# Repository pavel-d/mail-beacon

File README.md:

# Mail Beacon

The Mailbox Beacon is a device that detects when a new letter or package has been delivered to your mailbox using a reed switch. It sends a signal to your LoRa gateway, then the gateway sends a message via WiFi to MQTT server. It's designed to integrate with HomeAssistant, but can theoretically work with anything that supports MQTT based sensors.

Specification
--
- Microcontroller: Attiny1616
- Radio module: SX1278 LoRa 433 Mhz (Ai-Thinker-Ra-01)
- Sensor: Reed switch
- Voltage regulator: SPX3819M5-L-3-3
- Programming Protocol: UPDI
- Power consumption: in microamps range when asleep
- Gateway: LILYGO TTGO LoRa32 V2.1
- Status LED

Wiring
--
Reed switch (or any other kind of contact switch) must be connected either to PA4 or PA7 pins and to the GND. Pins have internal pull-ups enabled and are "active low", so the switch must pull the pin to the ground when circuit is closed. Both pins have interrupts attached, microcontroller will send a message to the gateway when the logic level changes.

TEST button also has an interrupt attached and can be used to test the setup.

Power LED has a jumper that can be cut to reduce the power consumption.

Battery monitoring
--
The beacon sends the battery voltage (in milivolts) in every LoRa packet, so that you know when you need to re-charge the battery.

Schematic
--

Board
--

Images
--

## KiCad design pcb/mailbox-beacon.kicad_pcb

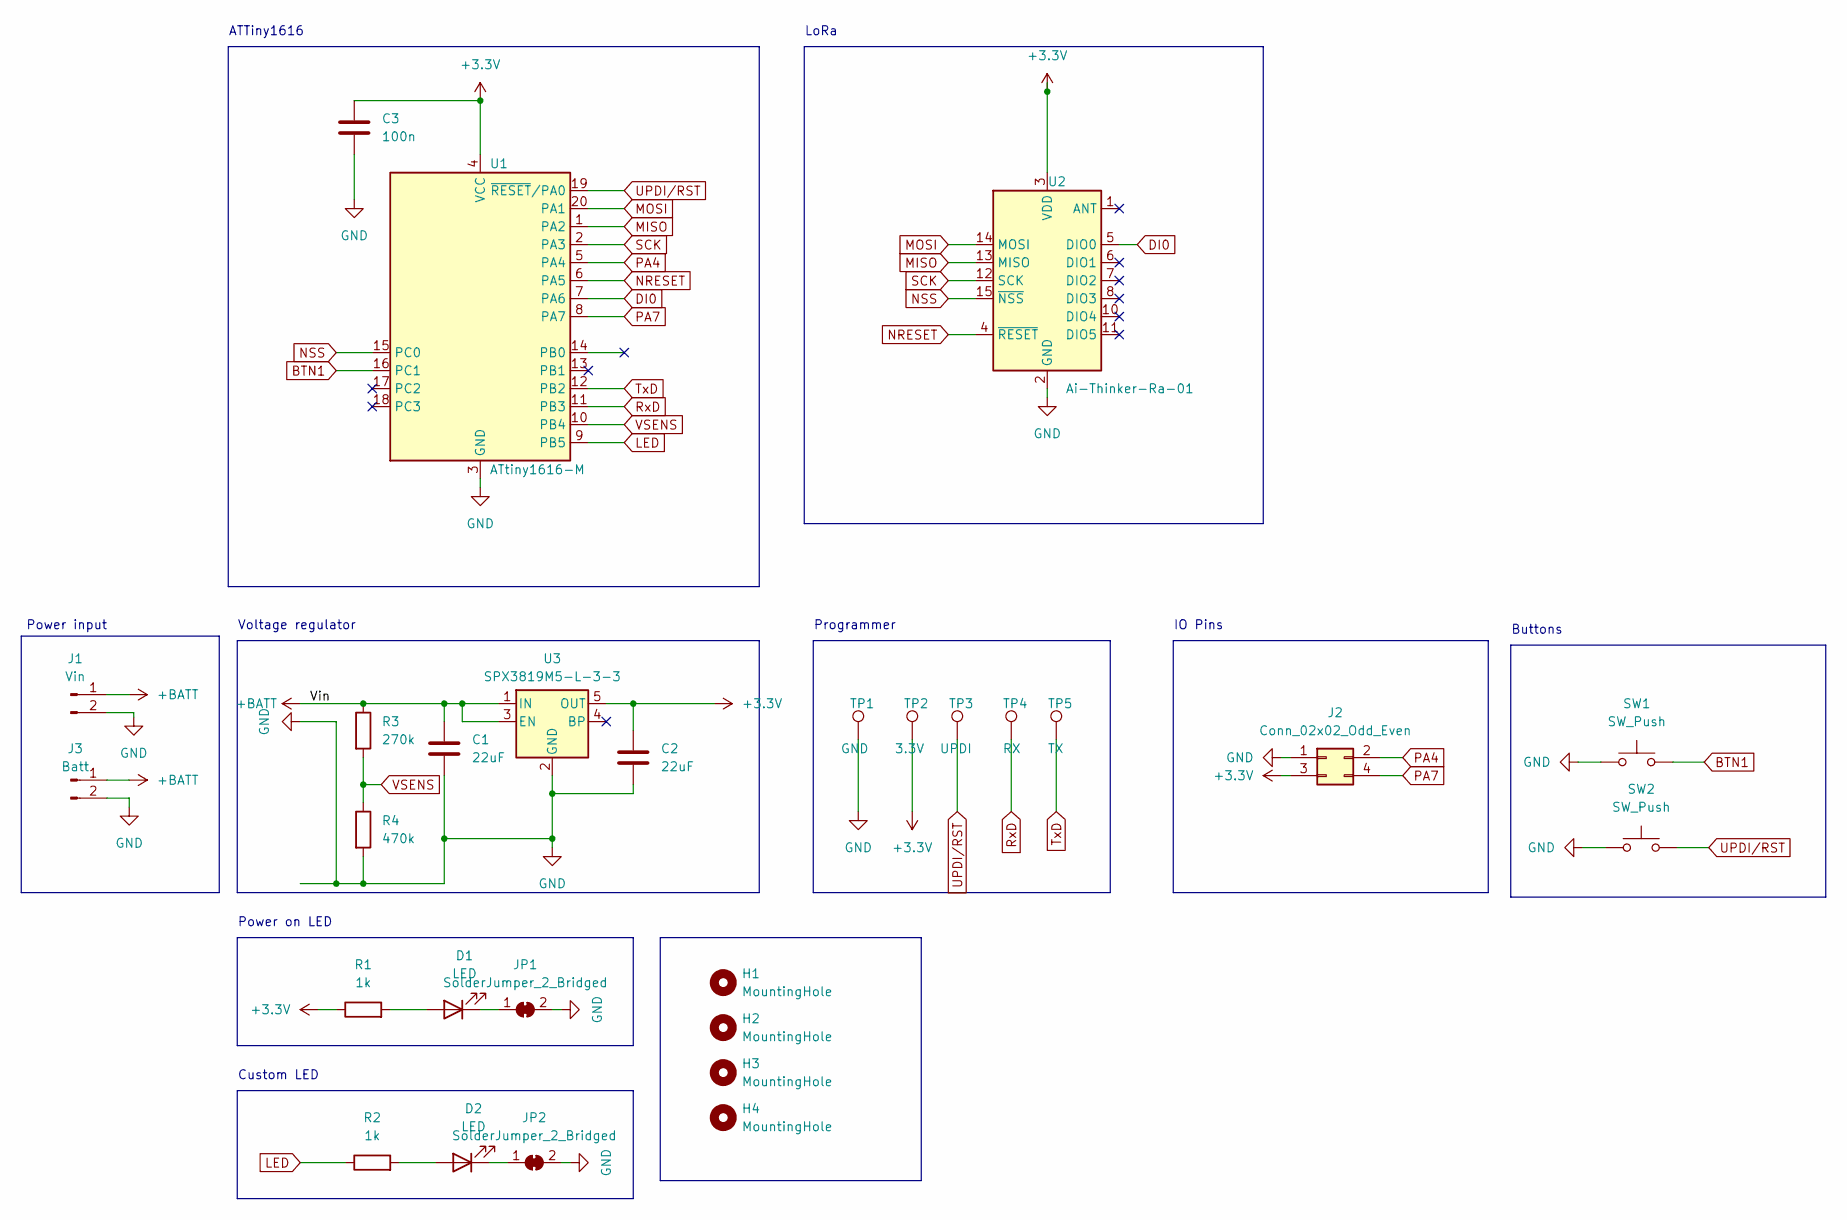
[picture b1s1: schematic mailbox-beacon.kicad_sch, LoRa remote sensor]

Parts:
C1, C2: 22uF; C_0805_2012Metric
C3: 100n; C_0805_2012Metric
D1, D2: LED; LED_0805_2012Metric
H1, H2, H3, H4: MountingHole; MountingHole_2.2mm_M2_Pad
J1: Vin; PinHeader_1x02_P2.54mm_Vertical
J2: Conn_02x02_Odd_Even; PinHeader_2x02_P2.54mm_Vertical
J3: Batt; JST_PH_S2B-PH-K_1x02_P2.00mm_Horizontal
JP1, JP2: SolderJumper_2_Bridged; SolderJumper-2_P1.3mm_Bridged_RoundedPad1.0x1.5mm
R1, R2: 1k; R_0805_2012Metric
R3: 270k; R_0805_2012Metric
R4: 470k; R_0805_2012Metric
SW1, SW2: SW_Push; SW_SPST_B3U-1000P
TP1: GND; TestPoint_Pad_D1.5mm
TP2: 3.3V; TestPoint_Pad_D1.5mm
TP3: UPDI; TestPoint_Pad_D1.5mm
TP4: RX; TestPoint_Pad_D1.5mm
TP5: TX; TestPoint_Pad_D1.5mm
U1: ATtiny1616-M; VQFN-20-1EP_3x3mm_P0.4mm_EP1.7x1.7mm
U2: Ai-Thinker-Ra-01; Ai-Thinker-Ra-01-LoRa
U3: SPX3819M5-L-3-3; SOT-23-5

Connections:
+3.3V: C2.1, C3.1, J2.3, R1.1, TP2.1, U1.4 (VCC), U2.3 (VDD), U3.5 (OUT)
+BATT: C1.1, J1.1, J3.1, R3.1, U3.1 (IN), U3.3 (EN)
BTN1: SW1.2, U1.16 (PC1)
DI0: U1.7 (PA6), U2.5 (DIO0)
GND: C1.2, C2.2, C3.2, J1.2, J2.1, J3.2, JP1.2 (B), JP2.2 (B), R4.2, SW1.1, SW2.1, TP1.1, U1.3 (GND), U1.21 (GND), U2.2 (GND), U2.9 (GND), U2.16 (GND), U3.2 (GND)
LED: R2.1, U1.9 (PB5)
MISO: U1.1 (PA2), U2.13 (MISO)
MOSI: U1.20 (PA1), U2.14 (MOSI)
NRESET: U1.6 (PA5), U2.4 (~RESET)
NSS: U1.15 (PC0), U2.15 (~NSS)
unnamed: D1.2 (A), R1.2
unnamed: D1.1 (K), JP1.1 (A)
unnamed: D2.2 (A), R2.2
unnamed: D2.1 (K), JP2.1 (A)
PA4: J2.2, U1.5 (PA4)
PA7: J2.4, U1.8 (PA7)
RxD: TP4.1, U1.11 (PB3)
SCK: U1.2 (PA3), U2.12 (SCK)
TxD: TP5.1, U1.12 (PB2)
UPDI/RST: SW2.2, TP3.1, U1.19 (~RESET/PA0)
VSENS: R3.2, R4.1, U1.10 (PB4)

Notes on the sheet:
Voltage regulator
IO Pins
Programmer
Buttons
Power on LED
Custom LED
Power input
LoRa
ATTiny1616

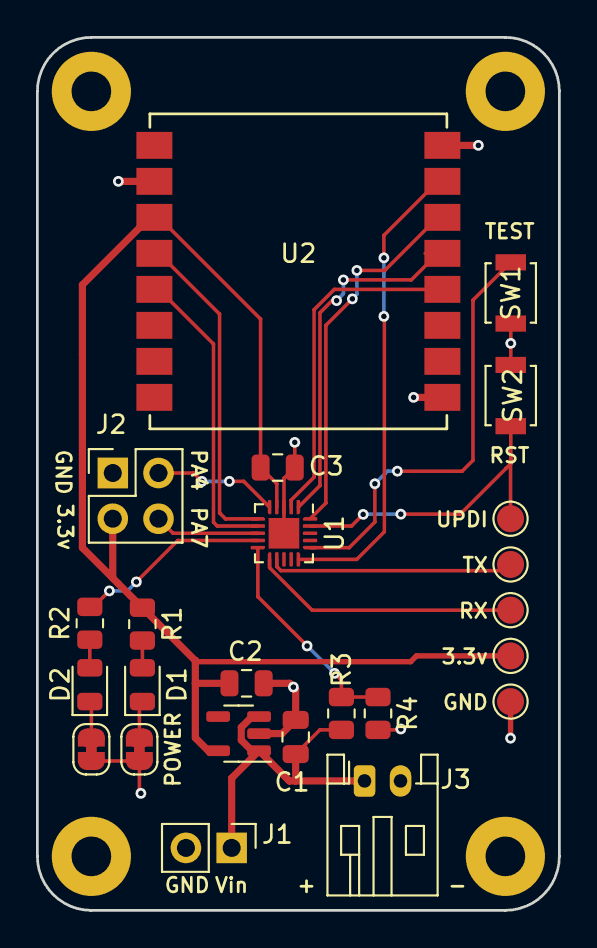
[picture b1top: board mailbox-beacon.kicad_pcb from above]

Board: 2 copper layers, 29.0 x 48.5 mm, 28 parts (0 on the bottom side), 21 nets.

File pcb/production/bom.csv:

Designator,Footprint,Quantity,Value,LCSC Part #
"C1, C2",0805,2,22uF,
C3,0805,1,100n,
"D1, D2",0805,2,LED,
"H1, H2, H3, H4",MountingHole_2.2mm_M2_Pad,4,MountingHole,
J1,PinHeader_1x02_P2.54mm_Vertical,1,Vin,
J2,PinHeader_2x02_P2.54mm_Vertical,1,Conn_02x02_Odd_Even,
J3,JST_PH_S2B-PH-K_1x02_P2.00mm_Horizontal,1,Batt,
"JP1, JP2",SolderJumper-2_P1.3mm_Bridged_RoundedPad1.0x1.5mm,2,SolderJumper_2_Bridged,
"R1, R2",0805,2,1k,
R3,0805,1,10k,
R4,0805,1,20k,
"SW1, SW2",SW_SPST_B3U-1000P,2,SW_Push,
TP1,TestPoint_Pad_D1.5mm,1,GND,
TP2,TestPoint_Pad_D1.5mm,1,3.3V,
TP3,TestPoint_Pad_D1.5mm,1,UPDI,
TP4,TestPoint_Pad_D1.5mm,1,RX,
TP5,TestPoint_Pad_D1.5mm,1,TX,
U1,VQFN-20-1EP_3x3mm_P0.4mm_EP1.7x1.7mm,1,ATtiny1616-M,
U2,Ai-Thinker-Ra-01-LoRa,1,Ai-Thinker-Ra-01,
U3,SOT-23-5,1,SPX3819M5-L-3-3,

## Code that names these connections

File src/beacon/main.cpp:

#include <Arduino.h>
#include <SPI.h>
#include <LoRa.h>
#include <avr/sleep.h>
#include <OneButton.h>
#include <EEPROM.h>
#include "Beacon.h"
#include "Blink.h"
#include "Packet.h"

#define SyncWord 0xF3
#define TxPower 20
#define SignalBandwidth 125E3
#define SpreadingFactor 12
#define BAND 433E6  

#define NSS 10
#define MOSI 14
#define MISO 15
#define SCK 16

#define NRESET 1
#define DI01 2

#define BTN1 11
#define PA4 0
#define PA7 3
#define LED 4
#define VSENS 5

#define BEACON_ID_ADDRESS 0x00

long wokeUpAt;
bool shouldTransmit;
uint8_t beaconID[PACKET_BEACON_ID_SIZE];
enum BeaconMode { TRANSMIT = 0, RESET = 2};

// TRANSMIT is default
BeaconMode beaconMode = TRANSMIT;

// Calculated using linear regression
// Due to chosen resistor dividors values and min voltage reg value, the actual range
// is between 3300 and 4800 millivolts
float voltageMultiplier = 4813.6192;
float voltageIntercept = -10.7395;

void sleep() {
  Serial.flush();
  LoRa.sleep();
  set_sleep_mode(SLEEP_MODE_PWR_DOWN);
  sleep_enable();
  sleep_cpu();
}


void onClick() {
  shouldTransmit = true;
  sleep_disable();
}

void onLongPress() {
  beaconMode = RESET;
}

OneButton button(BTN1);
Beacon beacon;

void handleButtonInterrupt() {
  wokeUpAt = millis();
  button.tick();
}

void handleExternalTrigger() {
  shouldTransmit = true;
  sleep_disable();
}

void initBeaconID(bool force) {
  if (!force) {
    EEPROM.get(BEACON_ID_ADDRESS, beaconID);

    for (int i = 0; i < PACKET_BEACON_ID_SIZE; i++) {
      if (beaconID[i] != 0) {
        return; // Address has been previously initialized, no need to re-assign
      }
    }
  }

  // Generate a random ID and save to EEPROM
  randomSeed(analogRead(PIN_PB0));

  for (int i = 0; i < PACKET_BEACON_ID_SIZE; i++) {
    beaconID[i] = random(256);
  }

  EEPROM.put(BEACON_ID_ADDRESS, beaconID);
}

void setup() {
  initBeaconID(false);

  beacon.setBeaconID(beaconID);

  Serial.begin(9600);

  analogReference(VDD);
  pinMode(LED, OUTPUT);
  pinMode(PA4, INPUT_PULLUP);
  pinMode(PA7, INPUT_PULLUP);

  attachInterrupt(digitalPinToInterrupt(BTN1), handleButtonInterrupt, CHANGE);
  attachInterrupt(digitalPinToInterrupt(PA4), handleExternalTrigger, CHANGE);
  attachInterrupt(digitalPinToInterrupt(PA7), handleExternalTrigger, CHANGE);

  button.attachClick(onClick);
  button.attachLongPressStart(onLongPress);
  button.attachDoubleClick(onLongPress);

  blink(LED);
  delay(500);

  LoRa.setPins(NSS, NRESET, DI01);
  LoRa.setSpreadingFactor(SpreadingFactor);
  LoRa.setSignalBandwidth(SignalBandwidth);
  LoRa.setSyncWord(SyncWord);
  LoRa.setTxPower(TxPower);
  
  delay(2000);

  if (!LoRa.begin(BAND)) {
    while (1) {
      blinkSlow(LED);
    }
  }

  Serial.println("Ready");

  blink(LED, 3);
}



void loop() {
  button.tick();

  switch (beaconMode)  {
  case TRANSMIT:
    if (shouldTransmit) {
      float val = float(analogReadEnh(VSENS, 12)) / float(4096);
      float miliVolts = val * voltageMultiplier + voltageIntercept;

      // When the device is connected via the programming header,
      // the voltage reading will be off
      if (miliVolts < 0) {
        miliVolts = 0;
      }

      if (beacon.transmit(digitalRead(PA4), digitalRead(PA7), digitalRead(BTN1), (uint16_t)miliVolts)) {
        blink(LED, 2);
      }

      shouldTransmit = false;
    }

    // Stay awake to correctly handle long button press
    if (millis() - wokeUpAt > 2000) {
      sleep();
    }

    break;

  case RESET:
    initBeaconID(true);
    beaconMode = TRANSMIT;
    blinkSlow(5);

  default:
    // This should never happen
    break;
  }
}

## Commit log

2023-12-23 Import
